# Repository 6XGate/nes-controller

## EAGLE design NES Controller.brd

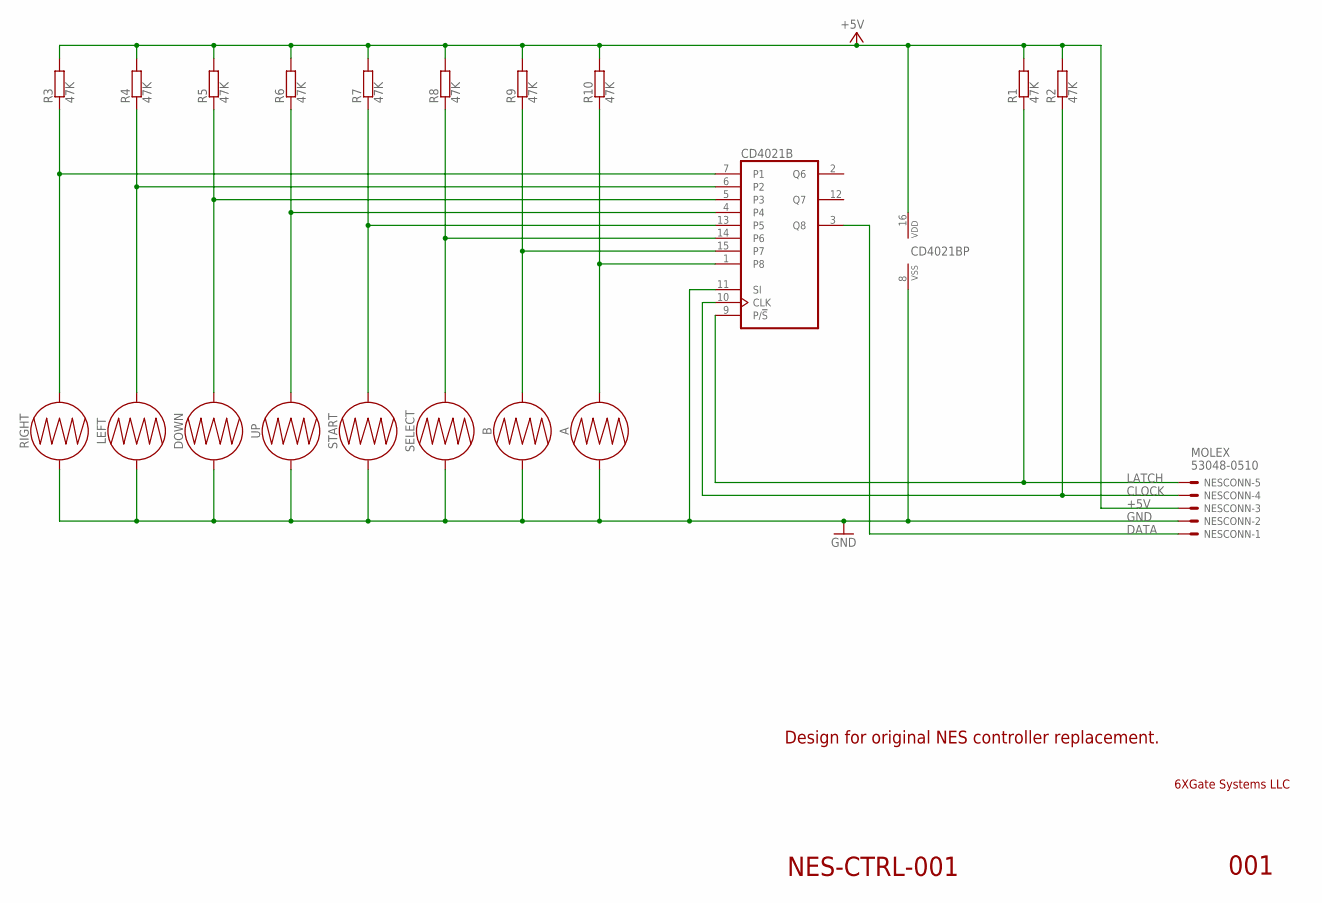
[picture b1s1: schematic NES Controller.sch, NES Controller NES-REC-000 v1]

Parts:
A: BUTTON-CONDUCTIVESMD; BUTTON-CONDUCTIVE
B: BUTTON-CONDUCTIVESMD; BUTTON-CONDUCTIVE
CD4021B: 4021D; SO16
DOWN: BUTTON-CONDUCTIVESMD; BUTTON-CONDUCTIVE
LEFT: BUTTON-CONDUCTIVESMD; BUTTON-CONDUCTIVE
NESCONN: 53048-05
R1, R2, R3, R4, R5, R6, R7, R8, R9, R10: 47K; R0805
RIGHT: BUTTON-CONDUCTIVESMD; BUTTON-CONDUCTIVE
SELECT: BUTTON-CONDUCTIVESMD; BUTTON-CONDUCTIVE
START: BUTTON-CONDUCTIVESMD; BUTTON-CONDUCTIVE
UP: BUTTON-CONDUCTIVESMD; BUTTON-CONDUCTIVE

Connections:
+5V: CD4021B.16 (VDD), NESCONN.3, R1.2, R2.2, R3.2, R4.2, R5.2, R6.2, R7.2, R8.2, R9.2, R10.2
A: A.1, CD4021B.1 (P8), R10.1
B: B.1, CD4021B.15 (P7), R9.1
CLOCK: CD4021B.10 (CLK), NESCONN.4, R2.1
DATA: CD4021B.3 (Q8), NESCONN.1
DOWN: CD4021B.5 (P3), DOWN.2, R5.1
GND: A.2, B.2, CD4021B.8 (VSS), CD4021B.11 (SI), DOWN.1, LEFT.2, NESCONN.2, RIGHT.1, SELECT.2, START.1, UP.1
LATCH: CD4021B.9 (P/!S), NESCONN.5, R1.1
LEFT: CD4021B.6 (P2), LEFT.1, R4.1
RIGHT: CD4021B.7 (P1), R3.1, RIGHT.2
SELECT: CD4021B.14 (P6), R8.1, SELECT.1
START: CD4021B.13 (P5), R7.1, START.2
UP: CD4021B.4, R6.1, UP.2

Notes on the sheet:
Design for original NES controller replacement.

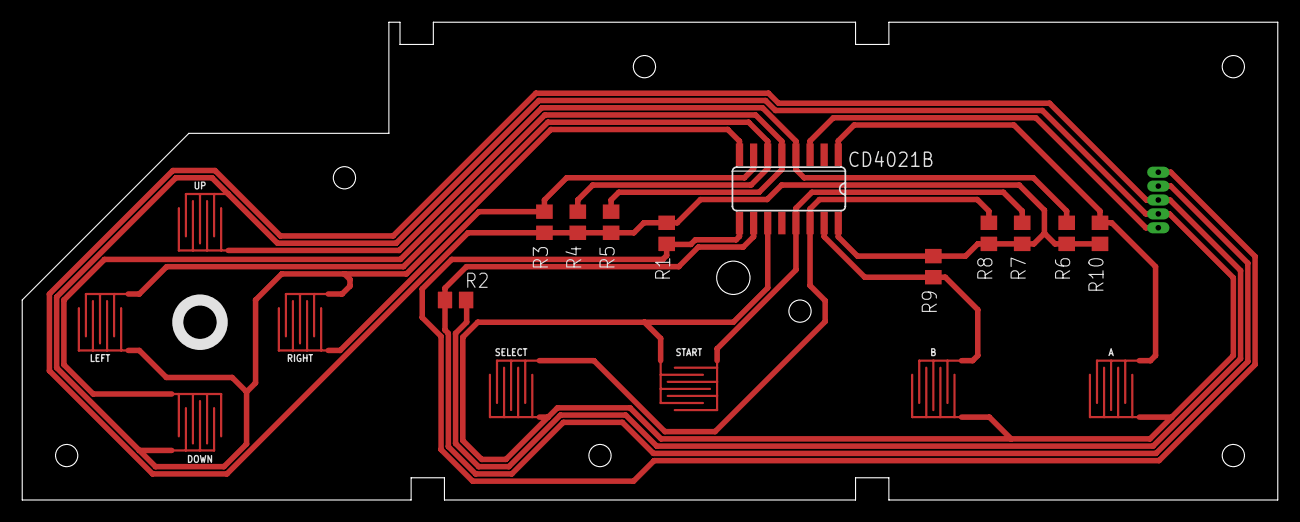
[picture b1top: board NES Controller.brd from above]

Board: 2 copper layers, 113.0 x 43.0 mm, 20 parts (1 on the bottom side), 13 nets.

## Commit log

2018-12-31 R001 Schematic and Board
2018-12-31 Cleaned Up Some Traces
    - Also add ignores for the back-up files.

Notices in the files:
parts and their libraries:
SparkFun-Switches: Licensing: Creative Commons ShareAlike 4.0 International - https://creativecommons.org/licenses/by-sa/4.0
